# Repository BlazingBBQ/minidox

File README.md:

Remake of That-Canadian's [MiniDox_PCB](https://github.com/That-Canadian/MiniDox_PCB). Schematic and PCB remade, with some custom changes such as:
- Main thumb key changed to 1.5u. Standard ANSI 61 key layout only includes 1x 1.75u keycaps, however there are 2x 1.5u keycaps on the same row.
- Added case mounting holes. Added 4mm wide drill hole to fit standard M2 standoffs. Footprint also includes 2.2mm wide outline for the case laser cut guide.

### Generating Case Files
To generate case laser cut files:
1. Go to File > Export > SVG
1. Ensure the following settings are set:
- Print Mode: "Black and white"
- SVG Page Size: "Board area only"
- Pagination: "All layers in a single file"
1. For case, select Eco1.User and Edge.Cuts layers. For plate, select Eco1.User, Eco2.User and Edge.Cuts layers.
1. Click Export

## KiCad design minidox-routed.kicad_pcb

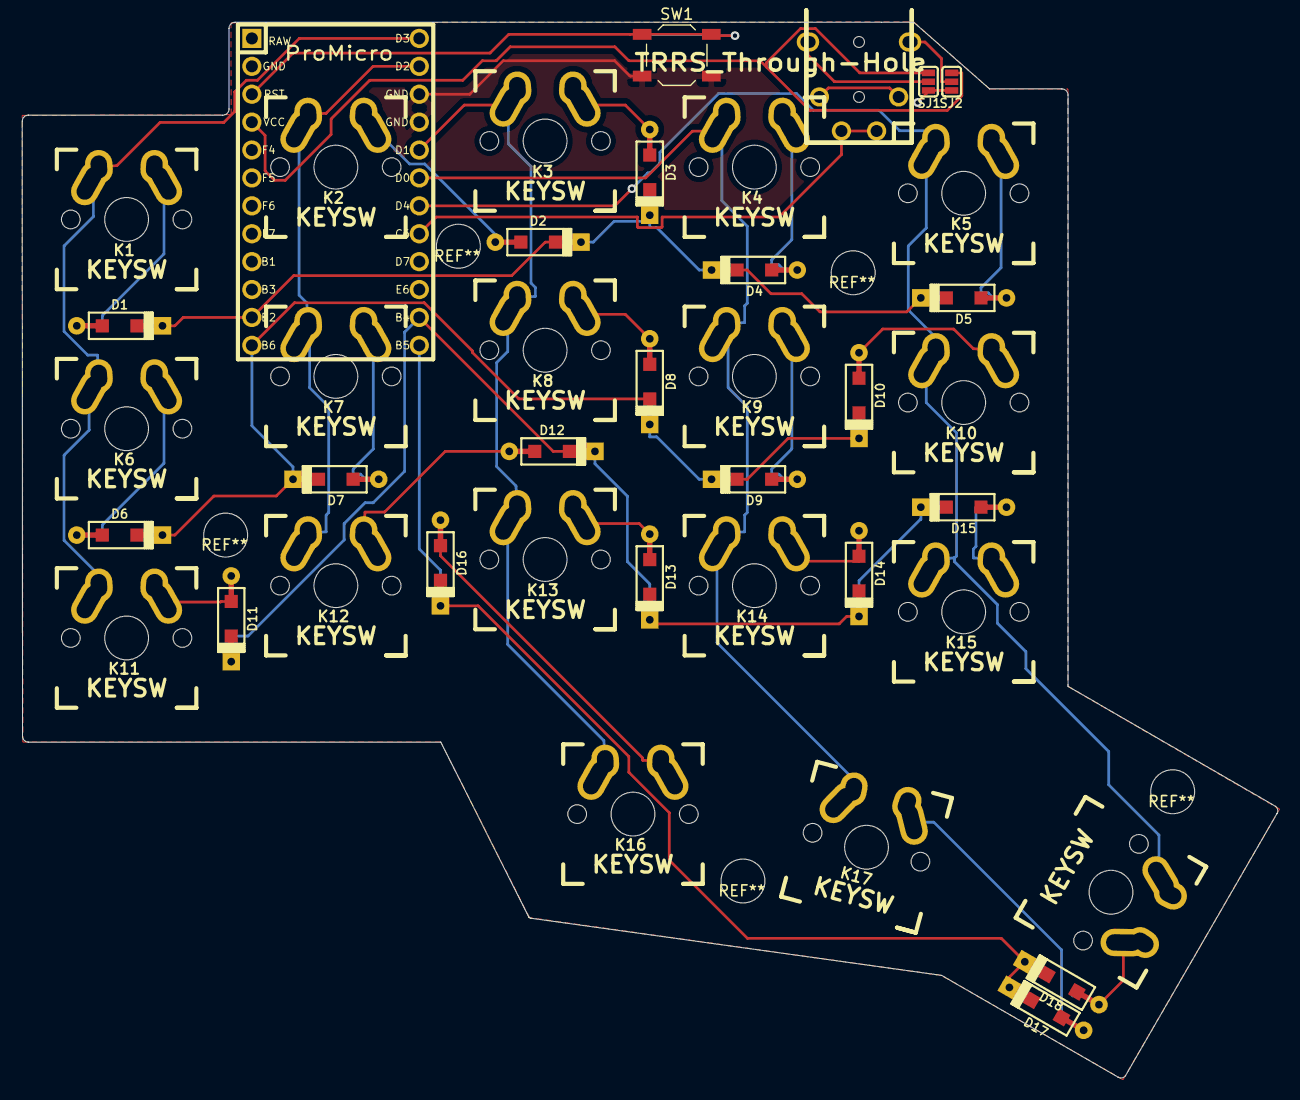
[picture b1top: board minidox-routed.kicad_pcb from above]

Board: 2 copper layers, 114.3 x 96.1 mm, 42 parts (1 on the bottom side), 33 nets.

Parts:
D1, D2, D3, D4, D5, D6, D7, D8, D9, D10, D11, D12, D13, D14, D15, D16, D17, D18: D; D_SOD123_axial-dual
K1, K2, K3, K4, K5, K6, K7, K8, K9, K10, K11, K12, K13, K14, K15, K16, K17: KEYSW; Mx_Alps_100-dualside
K18: KEYSW; Mx_Alps_150-dualsided
K19: TRRS_Through-Hole; 4pin35mmAudio-dualsided
SJ1, SJ2: SOLDER_JUMPER_3
SW1, SW1#2: SW_PUSH; SW_SPST_TL3342
U1: ProMicro; Pro_Micro

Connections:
/col1: K1.1, K6.1, K11.1, U1.13
/col2: K2.1, K7.1, K12.1, U1.14
/col3: K3.1, K8.1, K13.1, K16.1, U1.17
/col4: K4.1, K9.1, K14.1, K17.1, U1.18
/col5: K5.1, K10.1, K15.1, K18.1, U1.19
/data: K19.3, U1.20
/row1: D1.1, D2.1, D3.1, D4.1, D5.1, U1.11
/row2: D6.1, D7.1, D8.1, D9.1, D10.1, U1.12
/row3: D11.1, D12.1, D13.1, D14.1, D15.1, U1.23
/row4: D16.1, D17.1, D18.1, U1.24
GND: SJ1.3, SJ2.3, SW1.2, SW1#2.2, U1.2, U1.15, U1.16
unnamed: D1.2, K1.2
unnamed: D2.2, K2.2
unnamed: D3.2, K3.2
unnamed: D4.2, K4.2
unnamed: D5.2, K5.2
unnamed: D6.2, K6.2
unnamed: D7.2, K7.2
unnamed: D8.2, K8.2
unnamed: D9.2, K9.2
unnamed: D10.2, K10.2
unnamed: D11.2, K11.2
unnamed: D12.2, K12.2
unnamed: D13.2, K13.2
unnamed: D14.2, K14.2
unnamed: D15.2, K15.2
unnamed: D16.2, K16.2
unnamed: D17.2, K17.2
unnamed: D18.2, K18.2
unnamed: K19.1, SJ2.2
unnamed: K19.4, SJ1.2
unnamed: SW1.1, SW1#2.1, U1.3
VCC: SJ1.1, SJ2.1, U1.4

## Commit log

2020-04-21 Add README
2020-04-21 Update case files and instructions
